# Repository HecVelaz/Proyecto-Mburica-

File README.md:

# Proyecto-Mburica-
Repositorio central del Proyecto Mburicao: Sistema IoT de monitoreo de nivel de cauces, modelos de predicción con IA y documentación científica

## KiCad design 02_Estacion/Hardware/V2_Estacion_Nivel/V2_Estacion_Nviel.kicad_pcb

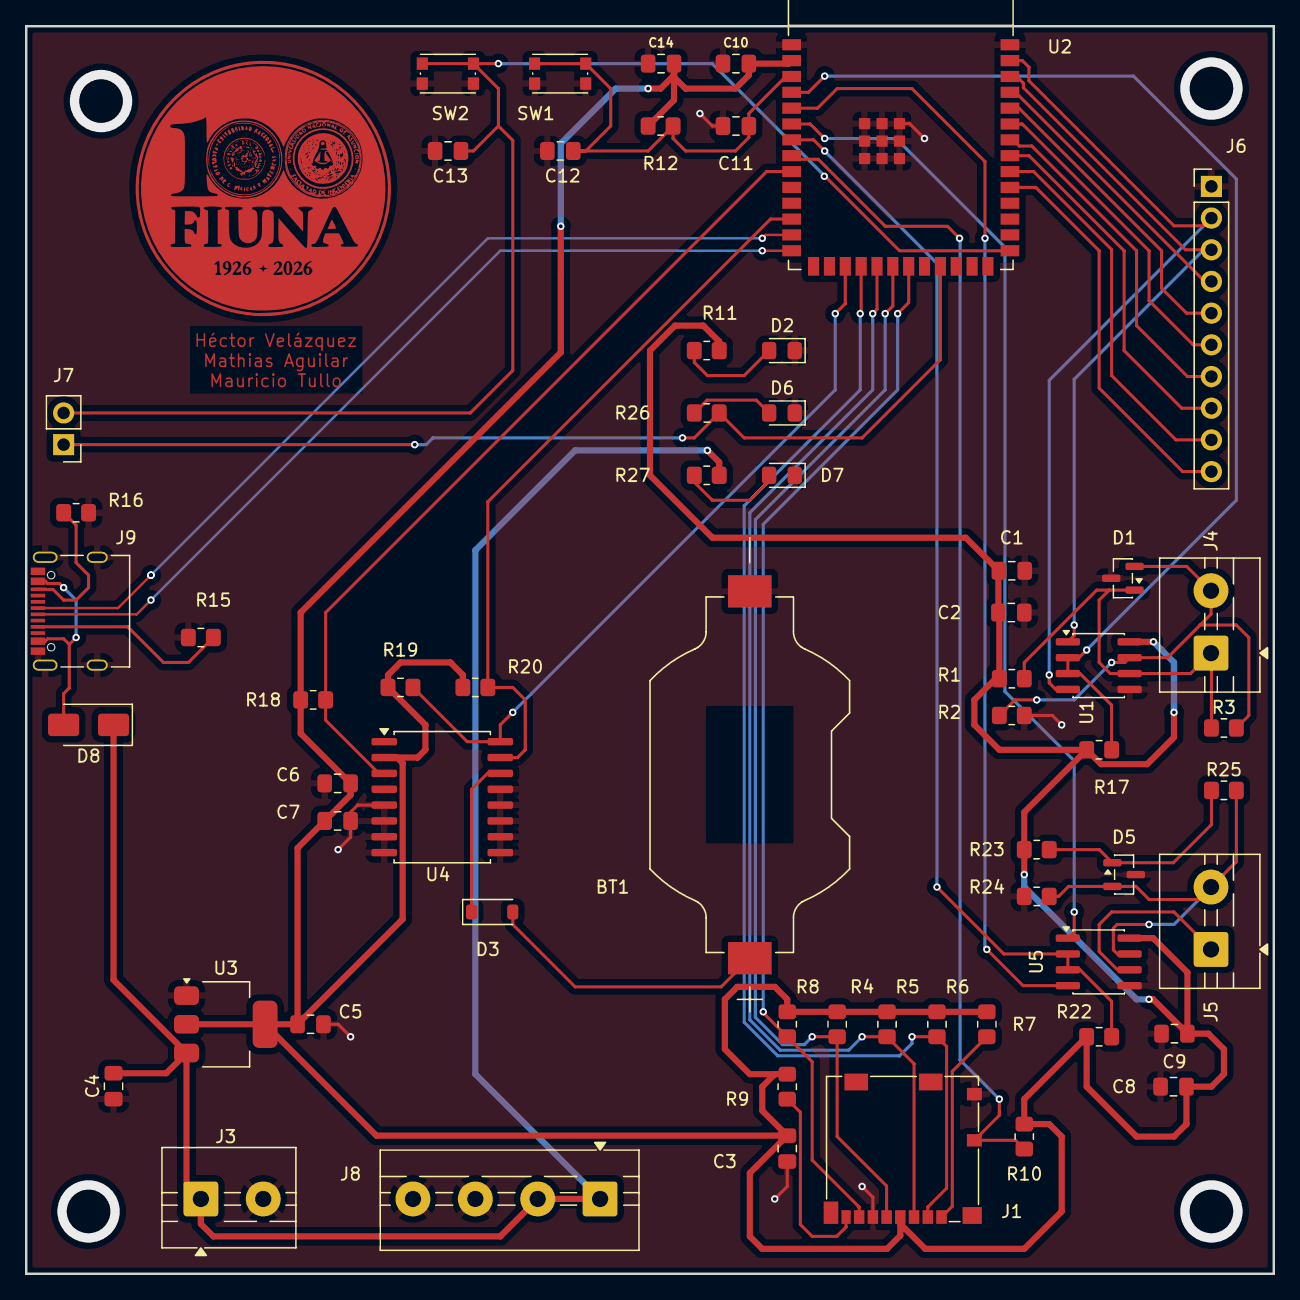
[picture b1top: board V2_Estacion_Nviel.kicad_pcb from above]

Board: 2 copper layers, 100.0 x 100.0 mm, 61 parts (0 on the bottom side), 43 nets.

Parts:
BT1: SMTU2032-LF; BAT_SMTU2032-LF
C1, C8: 0.1u; C_0805_2012Metric_Pad1.18x1.45mm_HandSolder
C2, C9: 10u; C_0805_2012Metric_Pad1.18x1.45mm_HandSolder
C3, C6, C7, C12, C13, C14: 0.1uF; C_0805_2012Metric_Pad1.18x1.45mm_HandSolder
C4: 10uF; C_0805_2012Metric_Pad1.18x1.45mm_HandSolder
C5, C10: 22uF; C_0805_2012Metric_Pad1.18x1.45mm_HandSolder
C11: 1uF; C_0805_2012Metric_Pad1.18x1.45mm_HandSolder
D1, D5: SM712_SOT23; SOT-23
D2: GREEN; LED_0805_2012Metric_Pad1.15x1.40mm_HandSolder
D3: 1N4148; D_SOD-123
D6: BLUE; LED_0805_2012Metric_Pad1.15x1.40mm_HandSolder
D7: RED; LED_0805_2012Metric_Pad1.15x1.40mm_HandSolder
D8: SS14; D_SMA
J1: Micro_SD_Card_Det1; microSD_HC_Molex_104031-0811
J3, J4, J5: Screw_Terminal_01x02; TerminalBlock_MaiXu_MX126-5.0-02P_1x02_P5.00mm
J6: Conn_01x10_Pin; PinHeader_1x10_P2.54mm_Vertical
J7: Conn_01x02_Pin; PinHeader_1x02_P2.54mm_Vertical
J8: Screw_Terminal_01x04; TerminalBlock_MaiXu_MX126-5.0-04P_1x04_P5.00mm
J9: USB_C_Receptacle_USB2.0_16P; USB_C_Receptacle_Palconn_UTC16-G
R1, R2, R17, R18, R19, R20, R22, R23, R24: 4.7k; R_0805_2012Metric_Pad1.20x1.40mm_HandSolder
R3, R25: 120; R_0805_2012Metric_Pad1.20x1.40mm_HandSolder
R4, R5, R6, R7, R8, R9, R10, R12: 10k; R_0805_2012Metric_Pad1.20x1.40mm_HandSolder
R11, R26, R27: 1k; R_0805_2012Metric_Pad1.20x1.40mm_HandSolder
R15, R16: 5.1k; R_0805_2012Metric_Pad1.20x1.40mm_HandSolder
SW1: RST; SW_Push_1P1T_NO_CK_KMR2
SW2: BOOT; SW_Push_1P1T_NO_CK_KMR2
U1, U5: SP3485EN; SOIC-8_3.9x4.9mm_P1.27mm
U2: ESP32-S3-WROOM-1
U3: AMS1117-3.3; SOT-223-3_TabPin2
U4: DS3231M; SOIC-16W_7.5x10.3mm_P1.27mm

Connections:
3V3: C1.1, C2.1, C3.2, C5.2, C6.2, C7.1, C8.1, C9.1, C10.2, C14.2, J1.4 (VDD), R1.1, R4.1, R5.1, R6.1, R7.1, R8.1, R9.1, R10.1, R11.1, R12.1, R17.1, R18.1, R19.1, R20.1, R22.1, R23.1, U1.8 (VCC), U2.2 (3V3), U3.2 (VO), U4.2 (VCC), U5.8 (VCC)
A1: D1.1 (A1), J4.1, R1.2, R3.1, U1.6 (A)
A2: D5.1 (A1), J5.1, R23.2, R25.1, U5.6 (A)
B1: D1.2 (A2), J4.2, R2.1, R3.2, U1.7 (B)
B2: D5.2 (A2), J5.2, R24.1, R25.2, U5.7 (B)
D+: J9.A6 (D+), U2.14 (GPIO20/U1CTS/ADC2_CH9/CLK_OUT1/USB_D+)
D-: J9.A7 (D-), U2.13 (GPIO19/U1RTS/ADC2_CH8/CLK_OUT2/USB_D-)
DE/RE 1: R17.2, U1.2 (~RE), U1.3 (DE), U2.4 (GPIO4/TOUCH4/ADC1_CH3)
DE/RE 2: R22.2, U2.7 (GPIO7/TOUCH7/ADC1_CH6), U5.2 (~RE), U5.3 (DE)
DI1: J6.2, U1.4 (DI), U2.39 (GPIO1/TOUCH1/ADC1_CH0)
DI2: U2.5 (GPIO5/TOUCH5/ADC1_CH4), U5.4 (DI)
ESP_EN: C11.2, C12.2, R12.2, SW1.1, U2.3 (EN)
ESP_IO: C13.2, J7.2, SW2.1, U2.27 (GPIO0/BOOT)
GND: BT1.N, C1.2, C2.2, C3.1, C4.1, C5.1, C6.1, C7.2, C8.2, C9.2, C10.1, C11.1, C12.1, C13.1, C14.1, D1.3 (common), D2.1 (K), D5.3 (common), D6.1 (K), D7.1 (K), J1.6 (VSS), J1.10 (SHIELD), J3.2, J6.1, J8.3, J8.4, J9.A1 (GND), J9.A12 (GND), J9.B1 (GND), J9.B12 (GND), J9.S1 (SHIELD), R2.2, R15.2, R16.1, R24.2, SW1.2, SW2.2, U1.5 (GND), U2.1 (GND), U2.40 (GND), U2.41 (GND), U3.1 (GND), U4.5 (GND), U4.6 (GND), U4.7 (GND), U4.8 (GND), U4.9 (GND), U4.10 (GND), U4.11 (GND), U4.12 (GND), U4.13 (GND), U5.5 (GND)
GPIO21: J7.1, R26.1, U2.23 (GPIO21)
GPIO38: J6.10, U2.31 (GPIO38/FSPIWP/SUBSPIWP)
GPIO39: J6.9, U2.32 (MTCK/GPIO39/CLK_OUT3/SUBSPICS1)
GPIO40: J6.8, U2.33 (MTDO/GPIO40/CLK_OUT2)
GPIO41: J6.7, U2.34 (MTDI/GPIO41/CLK_OUT1)
GPIO42: J6.6, U2.35 (MTMS/GPIO42)
unnamed: D2.2 (A), R11.2
unnamed: BT1.P, D3.2 (A)
unnamed: D3.1 (K), U4.14 (VBAT)
unnamed: D6.2 (A), R26.2
unnamed: D7.2 (A), R27.2
unnamed: D8.2 (A), J9.A4 (VBUS), J9.A9 (VBUS), J9.B4 (VBUS), J9.B9 (VBUS)
unnamed: J1.8 (DAT1), R9.2
unnamed: J1.1 (DAT2), R7.2
unnamed: J9.A5 (CC1), R15.1
unnamed: J9.B5 (CC2), R16.2
RO1: J6.3, U1.1 (RO), U2.38 (GPIO2/TOUCH2/ADC1_CH1)
RO2: U2.6 (GPIO6/TOUCH6/ADC1_CH5), U5.1 (RO)
SCL: R19.2, U2.17 (GPIO9/TOUCH9/ADC1_CH8/FSPIHD/SUBSPIHD), U4.16 (SCL)
SD CLK: J1.5 (CLK), R4.2, U2.20 (GPIO12/TOUCH12/ADC2_CH1/FSPICLK/FSPIIO6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)
SD CS: J1.2 (DAT3/CD), R6.2, U2.18 (GPIO10/TOUCH10/ADC1_CH9/FSPICS0/FSPIIO4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)
SD DET: J1.9 (DET), R10.2, U2.8 (GPIO15/U0RTS/ADC2_CH4/XTAL_32K_P)
SD MISO: J1.7 (DAT0), R8.2, U2.21 (GPIO13/TOUCH13/ADC2_CH2/FSPIQ/FSPIIO7/S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)
SD MOSI: J1.3 (CMD), R5.2, U2.19 (GPIO11/TOUCH11/ADC2_CH0/FSPID/FSPIIO5/S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)
SDA: R20.2, U2.12 (GPIO8/TOUCH8/ADC1_CH7/SUBSPICS1), U4.15 (SDA)
SQW: R18.2, U2.9 (GPIO16/U0CTS/ADC2_CH5/XTAL_32K_N), U4.3 (~INT/SQW)
U0RX: J6.5, U2.36 (U0RXD/GPIO44/CLK_OUT2)
U0TX: J6.4, U2.37 (U0TXD/GPIO43/CLK_OUT1)
VCC: C4.2, D8.1 (K), J3.1, J8.1, J8.2, R27.1, U3.3 (VI)

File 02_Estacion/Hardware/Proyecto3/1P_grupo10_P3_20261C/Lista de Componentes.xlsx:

Tipo de componente | Referencia | Cantidad | Valor | Mfr Part Number | Enlace(mouser)
Batería / Portapila | BT1 | 1 | SMTU2032-LF | 1060TR | https://www.mouser.com/ProductDetail/Keystone-Electronics/10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
Capacitor | C1,C8,C3,C6,C7,C12,C13,C14 | 8 | 0.1uF | GCM188R71C104KA37D | https://www.mouser.com/ProductDetail/Murata-Electronics/GCM1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
 | C11 | 1 | 1uF | GRM188R61A105KA61D | https://www.mouser.com/ProductDetail/Murata-Electronics/GRM1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
 | C2,C9 | 2 | 10uF | 81-GRT21BR61A106KE1L | https://www.mouser.com/ProductDetail/Murata-Electronics/GRT2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
 | C10 | 1 | 22uF | GRM21BR60J226ME39L | https://www.mouser.com/ProductDetail/Murata-Electronics/GRM2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
 | C4 | 1 | 10uf | 12063C106KAT2A | https://www.mouser.com/ProductDetail/KYOCERA-AVX/12063C106KA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
 | C5 | 1 | 22uf | T495C226K025AHE300 | https://www.mouser.com/ProductDetail/KEMET/T495C226K025AHE30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
Diodo TVS / Protección | D1,D5 | 2 | SM712_SOT23 | SM712-02HTG | https://www.mouser.com/ProductDetail/Littelfuse/SM712-02HTG?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
Diodo | D3 | 1 | 1N4148 | 1N4148W-7-F | https://www.mouser.com/ProductDetail/Diodes-Incorporated/1N4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
Diodo Schottky | D8 | 1 | SS14 | SS14 | https://www.mouser.com/ProductDetail/onsemi/SS14?qs=mVVXn4M5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
LED | D2 | 1 | GREEN | LTST-C190KGKT | https://www.mouser.com/ProductDetail/LITEON/LTST-C190KGKT?qs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
 | D6 | 1 | BLUE | LTST-C190TBKT | https://www.mouser.com/ProductDetail/LITEON/LTST-C190TBKT?qs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
 | D7 | 1 | RED | LTST-C190KRKT | https://www.mouser.com/ProductDetail/LITEON/LTST-C190KRKT?qs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
Conector | J1 | 1 | Micro_SD_Card_Det1 | 503398-1892 | https://www.mouser.com/ProductDetail/Molex/503398-1892?qs=b0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
 | J2,J3,J4,J5 | 4 | Screw_Terminal_01x02 | 1751248 | https://www.mouser.com/ProductDetail/Phoenix-Contact/1751248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
 | J6 | 1 | Conn_01x10_Pin | M20-9991045 | https://www.mouser.com/ProductDetail/Harwin/M20-9991045?qs=%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
 | J7 | 1 | Conn_01x02_Pin | M20-9990245 | https://www.mouser.com/ProductDetail/Harwin/M20-9990245?qs=J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
 | J8 | 1 | Conn_Jack_12V | RASM722PTR13X | https://www.mouser.com/ProductDetail/Switchcraft/RASM722PTR1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
 | J9 | 1 | USB_C_Receptacle_USB2.0_16P | USB4085-GF-A | https://www.mouser.com/ProductDetail/GCT/USB4085-GF-A?qs=KUo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 | simbolo snapmagic
R | R1,R2,R17,R18,R19,R20,R22,R23,R24 | 9 | 4.7k | RC0603FR-074K7L | https://www.mouser.com/ProductDetail/YAGEO/RC0603FR-074K7L?q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
 | R3,R25 | 2 | 120 | RC0603FR-07120RL | https://www.mouser.com/ProductDetail/YAGEO/RC0603FR-07120RL?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
 | R4,R5,R6,R7,R8,R9,R10,R12 | 8 | 10k | RC0603FR-0710KL | https://www.mouser.com/ProductDetail/YAGEO/RC0603FR-0710KL?q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
 | R11,R26,R27 | 3 | 1k | RC0603FR-071KL | https://www.mouser.com/ProductDetail/YAGEO/RC0603FR-071KL?qs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
 | R26 | 1 | 330 | RC0603FR-07330RL | https://www.mouser.com/ProductDetail/YAGEO/RC0603FR-07330RL?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
 | R15,R16 | 2 | 5.1k | RC0603FR-075K1L | https://www.mouser.com/ProductDetail/YAGEO/RC0603FR-075K1L?q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
Pulsador / Switch | SW1 | 1 | RST | B3U-1000P | https://www.mouser.com/ProductDetail/Omron-Electronics/B3U-1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
 | SW2 | 1 | BOOT | B3U-1000P | https://www.mouser.com/ProductDetail/Omron-Electronics/B3U-1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
Circuito integrado | U1,U5 | 2 | SP3485EN | SP3485EN-L/TR | https://www.mouser.com/ProductDetail/MaxLinear/SP3485EN-L-TR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
Módulo / Microcontrolador | U2 | 1 | ESP32-S3-WROOM-1 | ESP32-S3-WROOM-1-N16R8 | https://www.mouser.com/ProductDetail/Espressif-Systems/ESP32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
Regulador de voltaje | U3 | 1 | AMS1117-3.3 | LM1117MPX-3.3/NOPB | https://www.mouser.com/ProductDetail/Texas-Instruments/LM111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
RTC / Reloj en tiempo real | U4 | 1 | DS3231M | DS3231MZ+ | https://www.mouser.com/ProductDetail/Analog-Devices-Maxim-In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
OBSERVACIONES |  |  |  |  | PCB 4 capas
 | quitamos R4 de la sdcard |  | en la línea de clk no se conecta ninguna resistencia |  | capa 2 de GND
 | Regulador LM1117 Observación picos de corriente |  | se podria cambiar por un convertidor Buck |  | capa3 de 3v3
 | posibilidad de eliminar el diodo D3
 | Agrega una resistencia de 10k desde ESP_IO0 hacia 3V3.
 | Cambiar R26 de 1k a 330 ohms (para que se vea el LED D6).

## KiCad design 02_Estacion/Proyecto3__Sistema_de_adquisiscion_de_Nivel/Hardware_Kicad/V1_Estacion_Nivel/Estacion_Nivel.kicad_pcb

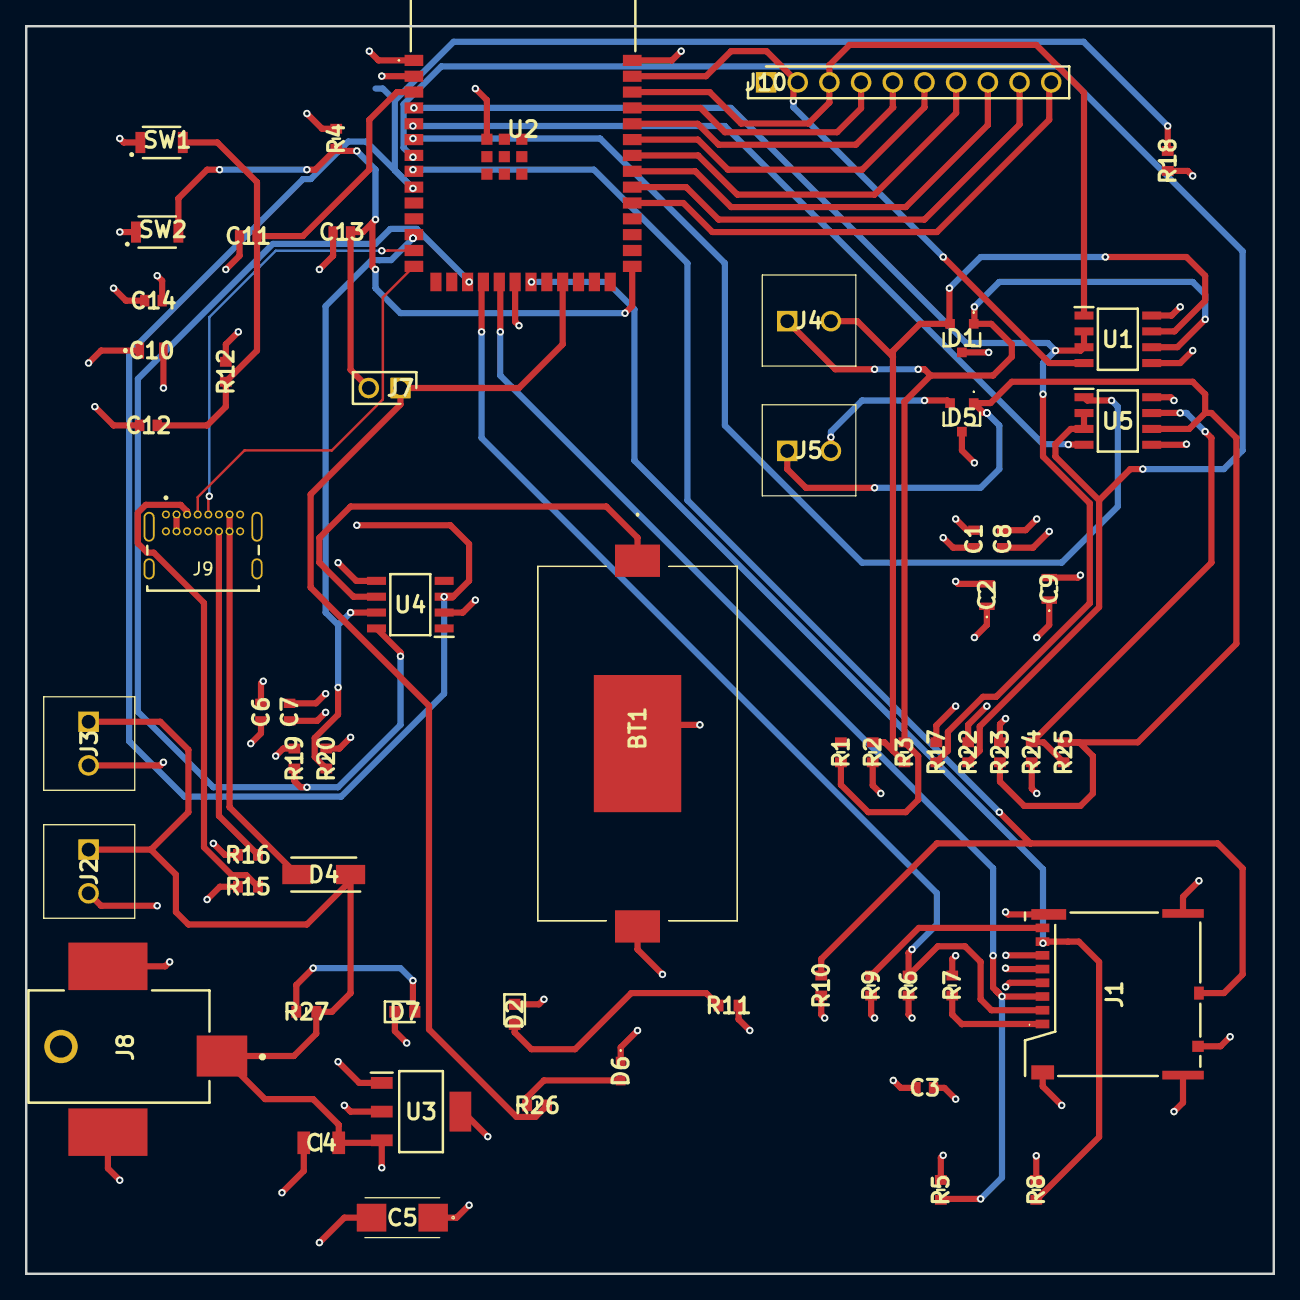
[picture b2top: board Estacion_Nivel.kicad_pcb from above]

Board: 4 copper layers, 100.0 x 100.0 mm, 61 parts (0 on the bottom side), 41 nets.

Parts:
BT1: 1060TR
C1, C3, C6, C7, C8, C12, C13, C14: 0.1uF; CAPC1608X90N
C2, C9: 10uF; GRT21BR61A106KE01L
C4: 10uF; CAPC3216X229N
C5: 22uF; T495C
C10: 22uF; GRM21BR60J226ME39L
C11: 1uF; CAPC1608X90N
D1, D5: SM712-02HTG; SM71202HTG
D2: LTST-C190KGKT; LEDC1608X80N
D4: SS14; DIOM5227X270N
D6: LTST-C190TBKT; LTSTC190TBKT
D7: LTST-C190KRKT; LEDC1608X80N
J1: 503398-1892; 5033981892
J2, J3, J4, J5: 1751248
J7: M20-9990245; HDRV2W64P0X254_1X2_508X254X864P
J8: RASM722PTR13X; RASM722X
J9: USB4085-GF-A_REVA4; GCT_USB4085-GF-A_REVA4
J10: M20-9991045; HDRV10W64P0X254_1X10_2540X254X864P
R1, R2, R17, R18, R19, R20, R22, R23, R24: 4.7k; RESC1608X55N
R3, R25: 120; RESC1608X55N
R4, R5, R6, R7, R8, R9, R10, R12: 10k; RESC1608X55N
R11, R27: 1K; RESC1608X55N
R15, R16: 5.1k; RESC1608X55N
R26: 330; RESC1608X55N
SW1: RST; B3U-1000P
SW2: BOOT; B3U-1000P
U1, U5: SP3485EN-L_TR; SOIC127P600X175-8N
U2: ESP32-S3-WROOM-1-N16R8; ESP32S3WROOM1N16R8
U3: LM1117MPX-3.3_NOPB; SOT230P700X180-4N
U4: DS3231MZ+; SOIC127P600X175-8N

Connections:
3V3: C1.2, C2.2, C3.2, C5.1 (+), C6.2, C7.1, C8.2, C9.2, C10.2, C14.2, J1.4 (VDD), J1.5 (CLK), R1.2, R4.2, R5.2, R6.2, R7.2, R8.2, R9.1, R10.1, R11.2, R12.2, R18.2, R19.2, R20.2, R23.2, U1.8 (VCC), U2.2 (3V3), U2.20 (IO12), U3.2 (OUTPUT), U3.4 (VOUT), U4.2 (VCC), U5.8 (VCC)
A1: D1.1, J4.1, R1.1, R3.2, U1.6 (A)
A2: D5.1, J5.1, R23.1, R25.2, U5.6 (A)
B1: D1.2, J4.2, R2.2, R3.1, U1.7 (B)
B2: D5.2, J5.2, R24.2, R25.1, U5.7 (B)
D+: J9.A6 (DP1), U2.14 (IO20)
D-: J9.A7 (DN1), U2.13 (IO19)
DE/RE 1: R17.1, U1.2 (~RE), U1.3 (DE), U2.4 (IO4)
DE/RE 2: R22.1, U2.7 (IO7), U5.2 (~RE), U5.3 (DE)
DI1: J10.2, U1.4 (DI), U2.39 (IO1)
DI2: U2.5 (IO5), U5.4 (DI)
ESP_EN: C11.2, C12.2, R12.1, SW1.2 (A), U2.3 (EN)
ESP_IO: C13.2, J7.2, R4.1, SW2.2 (A), U2.27 (IO0)
GND: BT1.2 (-), BT1.3 (EP), C1.1, C2.1, C3.1, C4.2, C5.2 (-), C6.1, C7.2, C8.1, C9.1, C10.1, C11.1, C12.1, C13.1, C14.1, D1.3, D2.1 (K), D5.3, D6.1 (K), D7.1 (K), J1.6 (VSS), J1.9 (DETECT_LEVER), J1.11, J1.12, J1.13, J1.14, J2.2, J3.2, J8.2 (SHUNT_TERMINAL), J8.3 (SLEEVE_TERMINAL), J9.A1 (GND), J9.A12 (GND), J9.B1 (GND), J9.B12 (GND), J9.S1 (SHELL), J9.S2 (SHELL), J9.S3 (SHELL), J9.S4 (SHELL), J10.1, R2.1, R15.2, R16.2, R17.2, R22.2, R24.1, SW1.1 (K), SW2.1 (K), U1.5 (GND), U2.1 (GND_1), U2.40 (GND_2), U2.41 (GND_3), U2.42 (GND_4), U2.43 (GND_5), U2.44 (GND_6), U2.45 (GND_7), U2.46 (GND_8), U2.47 (GND_9), U2.48 (GND_10), U2.49 (GND_11), U3.1 (ADJ/GND), U4.5 (GND), U5.5 (GND)
GPIO21: J7.1, R26.2, U2.23 (IO21)
GPIO38: J10.10, U2.31 (IO38)
GPIO39: J10.9, U2.32 (IO39)
GPIO40: J10.8, U2.33 (IO40)
GPIO41: J10.7, U2.34 (IO41)
GPIO42: J10.6, U2.35 (IO42)
unnamed: BT1.1 (+), U4.6 (VBAT)
unnamed: D2.2 (A), R11.1
unnamed: D6.2 (A), R26.1
unnamed: D7.2 (A), R27.1
unnamed: J1.8 (DAT1), R9.2
unnamed: J1.1 (DAT2), R7.1
unnamed: J9.A5 (CC1), R15.1
unnamed: J9.B5 (CC2), R16.1
RO1: J10.3, U1.1 (RO), U2.38 (IO2)
RO2: U2.6 (IO6), U5.1 (RO)
SCL: R19.1, U2.17 (IO9), U4.8 (SCL)
SD CS: J1.2 (CD/DAT3), R6.1, U2.18 (IO10)
SD DET: J1.10 (DETECT_SWITCH), R10.2, U2.8 (IO15)
SD MISO: J1.7 (DAT0), R8.1, U2.21 (IO13)
SD MOSI: J1.3 (CMD), R5.1, U2.19 (IO11)
SDA: R20.1, U2.12 (IO8), U4.7 (SDA)
SQW: R18.1, U2.9 (IO16), U4.3 (~INT/SQW)
U0RX: J10.5, U2.36 (RXD0)
U0TX: J10.4, U2.37 (TXD0)
VBUS: D4.2 (A), J9.A4 (VBUS), J9.A9 (VBUS), J9.B4 (VBUS), J9.B9 (VBUS)
VCC: C4.1, D4.1 (K), J2.1, J3.1, J8.1 (TIP_TERMINAL_(CENTER_PIN)), R27.2, U3.3 (INPUT)

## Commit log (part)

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2026-03-13 uodate
